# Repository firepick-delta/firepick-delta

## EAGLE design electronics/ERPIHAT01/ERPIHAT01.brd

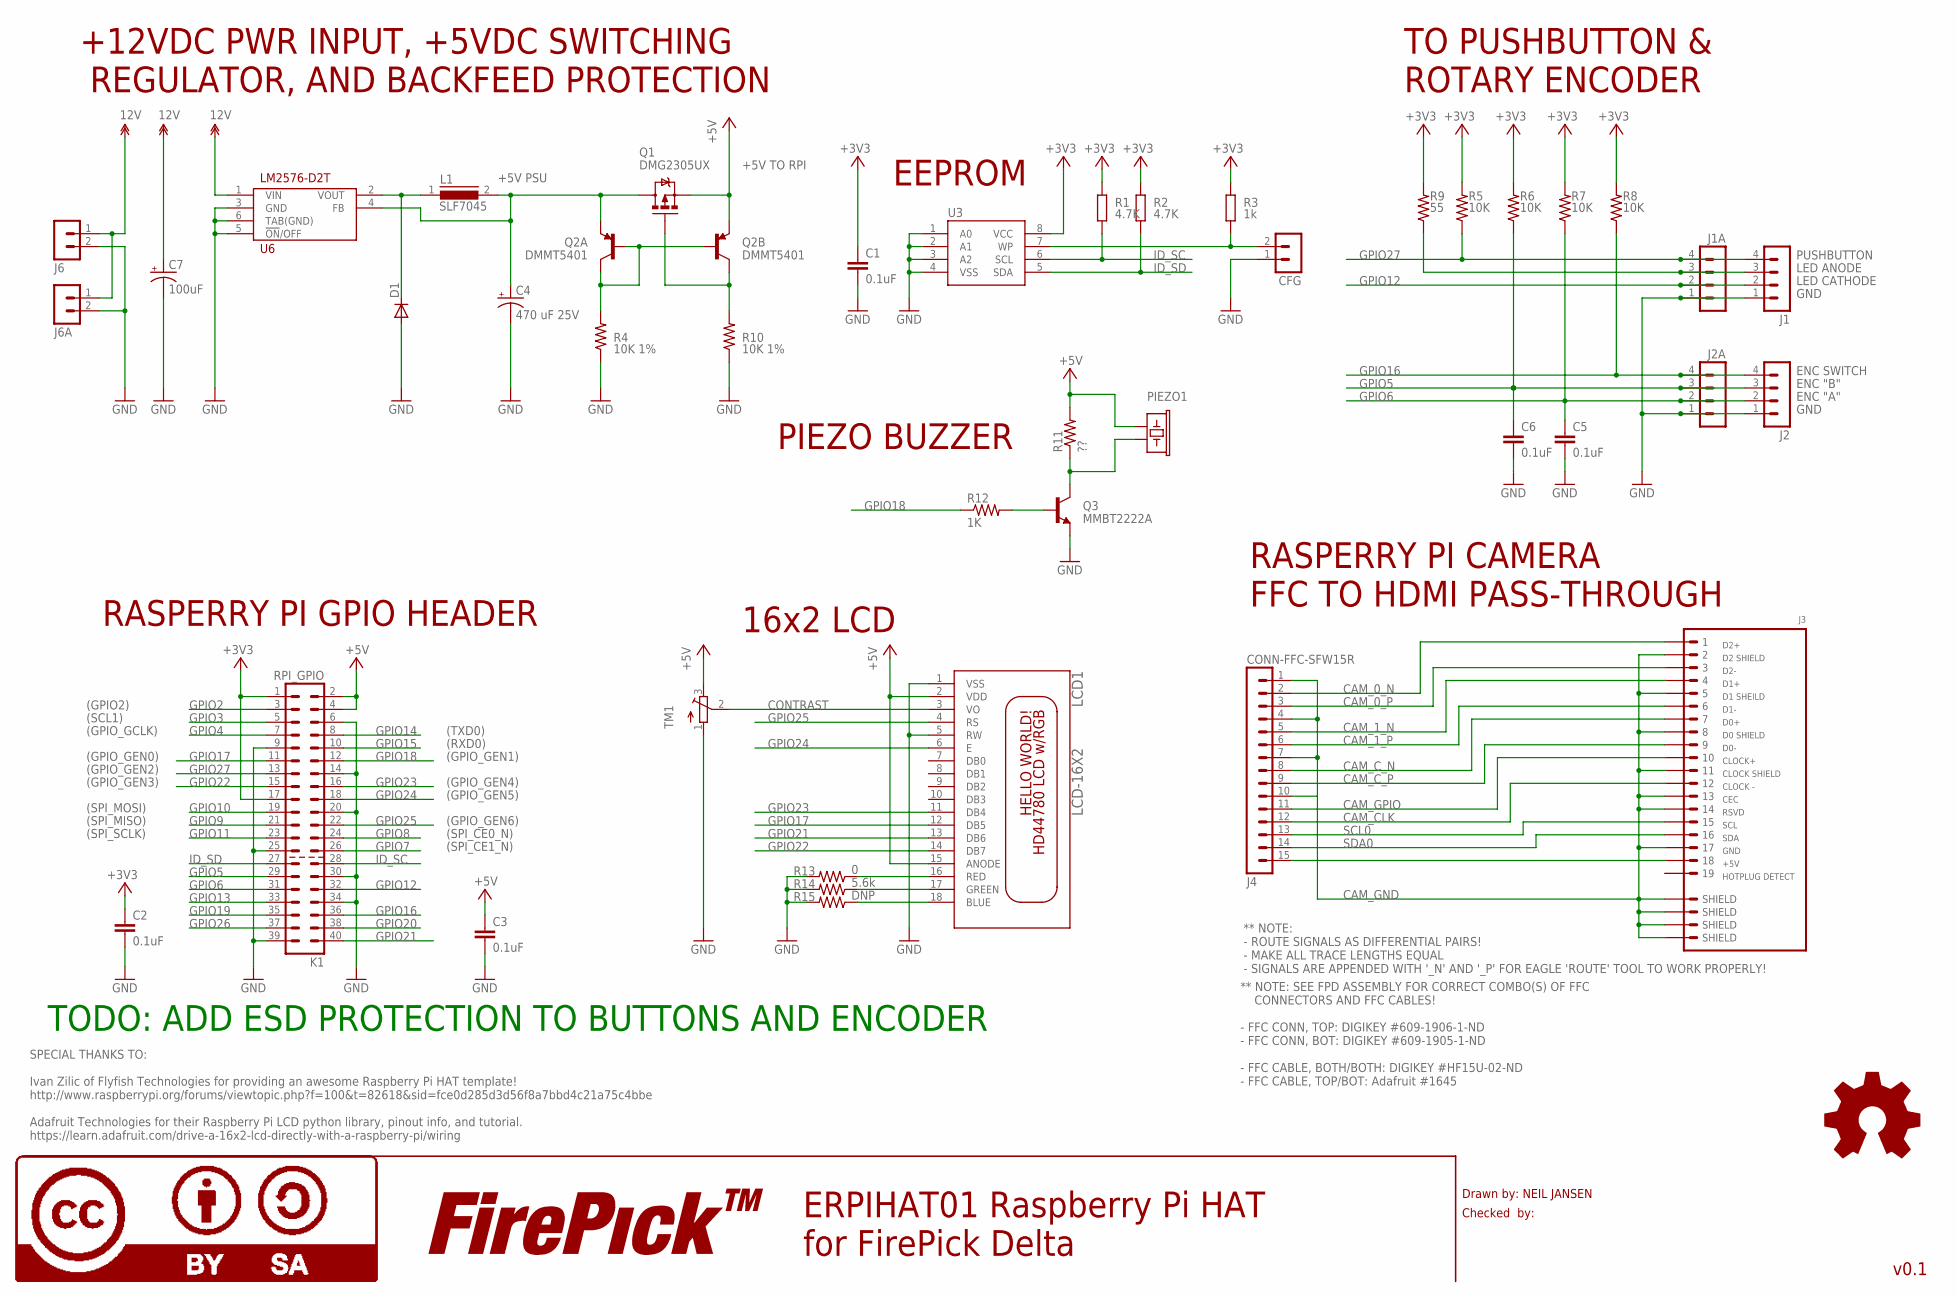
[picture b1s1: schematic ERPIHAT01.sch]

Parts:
C1, C2, C3: 0.1uF; C0805K
C4: 470 uF 25V; PANASONIC_D
C5, C6: 0.1uF; 0805
C7: 100uF; PANASONIC_D
CFG: MA02-1
D1: DIODE-DO-214AC; DO-214AC
J1, J2: CONN-RECT-4PINJST-PH-2MM; CONN-JST-PH_2.0MM_4PIN-SMT-RA
J1A, J2A: MA04-1
J3: CONN-HDMI; CON-HDMI-FCI-10029449-001RLF
J4: CONN-FFC-SFW15R; CON-FFC-SFW15R
J6: CONN-RECT-2PIN; CONN-JST_PH-2.0MM-2PIN-SMT-RA
J6A: MA02-1
K1: RPI_GPIO; PIN_20X2
L1: SLF7045
LCD1: LCD-16X2
LOGO1: LOGO-FIREPICK
LOGO2: LOGO-OSHWMEDIUM; LOGO-OSHW-MEDIUM
LOGO3: LOGO-CC-BY-SA
PIEZO1: BUZZERPTH; BUZZER-12MM
Q1: DMG2305UX; SOT23-3
Q2: DMMT5401; SOT23-6
Q3: MMBT2222A; SOT23-3
R1, R2: 4.7K; M0805; TOLERANCE 5%
R3: 1k; M0805; TOLERANCE 5%
R4, R10: 10K 1%; 0805
R5, R6, R7, R8: 10K; 0805
R9: 55; 0805
R11: ??; 0805
R12: 1K; 0805
R13: 0; 0805
R14: 5.6k; 0805
R15: DNP; 0805
TM1: TRIMPOTTC33X; TC33X
U3: EEPROM-I2CEIAJ; SO08-EIAJ
U6: LM2576-D2T; D2PAK

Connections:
12V: C7.+, J6.1, J6A.1, U6.1 (VIN)
+3V3: C1.1, C2.1, K1.1, K1.17, R1.2, R2.2, R3.2, R5.2, R6.2, R7.2, R8.2, R9.2, U3.8 (VCC)
+5V: C3.1, K1.2, K1.4, LCD1.2 (VDD), LCD1.15 (ANODE), PIEZO1.+ (1), Q1.2 (S), Q2.5 (E), R11.2, TM1.3 (E)
BLUE: LCD1.18 (BLUE), R15.1
BUZZ: PIEZO1.- (2), Q3.3 (C), R11.1
CAM_0_N: J3.1, J4.2
CAM_0_P: J3.3, J4.3
CAM_1_N: J3.4, J4.5
CAM_1_P: J3.6, J4.6
CAM_C_N: J3.7, J4.8
CAM_C_P: J3.9, J4.9
CAM_GND: J3.2, J3.5, J3.8, J3.11, J3.13, J3.14, J3.17, J3.SHIELD1 (SHIELD), J3.SHIELD2 (SHIELD), J3.SHIELD3 (SHIELD), J3.SHIELD4 (SHIELD), J4.1, J4.4, J4.7, J4.10
CAM_GPIOCLK_N: J3.10, J4.11
CAM_GPIOCLK_P: J3.12, J4.12
CAM_SCLSDA_N: J3.15, J4.13
CAM_SCLSDA_P: J3.16, J4.14
CONTRAST: LCD1.3 (VO), TM1.2 (S)
FEEDBACK: C4.+, L1.2, Q1.3 (D), Q2.6 (E), U6.4 (FB)
GND: C1.2, C2.2, C3.2, C4.-, C5.2, C6.2, C7.-, CFG.1, D1.A, J1.1, J1A.1, J2.1, J2A.1, J6.2, J6A.2, K1.6, K1.9, K1.14, K1.20, K1.25, K1.30, K1.34, K1.39, LCD1.1 (VSS), LCD1.5 (RW), Q3.2 (E), R4.1, R10.1, R13.2, R14.2, R15.2, TM1.1 (A), U3.1 (A0), U3.2 (A1), U3.3 (A2), U3.4 (VSS), U6.3 (GND), U6.5 (!ON!/OFF), U6.6 (TAB(GND))
GPIO2: K1.3
GPIO3: K1.5
GPIO4: K1.7
GPIO5: C6.1, J2.3, J2A.3, K1.29, R6.1
GPIO6: C5.1, J2.2, J2A.2, K1.31, R7.1
GPIO7: K1.26
GPIO8: K1.24
GPIO9: K1.21
GPIO10: K1.19
GPIO11: K1.23
GPIO12: J1.2, J1A.2, K1.32
GPIO13: K1.33
GPIO14: K1.8
GPIO15: K1.10
GPIO16: J2.4, J2A.4, K1.36, R8.1
GPIO17: K1.11, LCD1.12 (DB5)
GPIO18: K1.12, R12.1
GPIO19: K1.35
GPIO20: K1.38
GPIO21: K1.40, LCD1.13 (DB6)
GPIO22: K1.15, LCD1.14 (DB7)
GPIO23: K1.16, LCD1.11 (DB4)
GPIO24: K1.18, LCD1.6 (E)
GPIO25: K1.22, LCD1.4 (RS)
GPIO26: K1.37
GPIO27: J1.4, J1A.4, K1.13, R5.1
GREEN: LCD1.17 (GREEN), R14.1
ID_SC: K1.28, R1.1, U3.6 (SCL)
ID_SD: K1.27, R2.1, U3.5 (SDA)
unnamed: J3.18, J4.15
unnamed: Q2.1 (C), Q2.2 (B), Q2.3 (B), R4.2
unnamed: Q1.1 (G), Q2.4 (C), R10.2
unnamed: Q3.1 (B), R12.2
unnamed: CFG.2, R3.1, U3.7 (WP)
PANEL_LED_RED: J1.3, J1A.3, R9.1
RED: LCD1.16 (RED), R13.1
VOUT: D1.C, L1.1, U6.2 (VOUT)

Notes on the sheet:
Drawn by: NEIL JANSEN
Checked by:
SPECIAL THANKS TO: Ivan Zilic of Flyfish Technologies for providing an awesome Raspberry Pi HAT template! http://www.raspberrypi.org/forums/viewtopic.php?f=100&t=82618&sid=fce0d285d3d56f8a7bbd4c21a75c4bbe Adafruit Technologies for their Raspberry Pi LCD python library, pinout info, and tutorial. ht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
v0.1
(SPI_MOSI)
(SPI_MISO)
(SPI_SCLK)
(GPIO_GEN3)
(GPIO_GEN2)
(GPIO_GEN0)
(GPIO_GCLK)
(SCL1)
(GPIO2)
(TXD0)
(RXD0)
(GPIO_GEN1)
(GPIO_GEN4)
(GPIO_GEN5)
(GPIO_GEN6)
(SPI_CE0_N)
(SPI_CE1_N)
+5V TO RPI
+5V PSU
** NOTE: SEE FPD ASSEMBLY FOR CORRECT COMBO(S) OF FFC CONNECTORS AND FFC CABLES! - FFC CONN, TOP: DIGIKEY #609-1906-1-ND - FFC CONN, BOT: DIGIKEY #609-1905-1-ND - FFC CABLE, BOTH/BOTH: DIGIKEY #HF15U-02-ND - FFC CABLE, TOP/BOT: Adafruit #1645
PUSHBUTTON
GND
ENC "A"
ENC "B"
ENC SWITCH
LED ANODE
LED CATHODE
** NOTE: - ROUTE SIGNALS AS DIFFERENTIAL PAIRS! - MAKE ALL TRACE LENGTHS EQUAL - SIGNALS ARE APPENDED WITH '_N' AND '_P' FOR EAGLE 'ROUTE' TOOL TO WORK PROPERLY!
CAM_GPIO
CAM_CLK
SCL0
SDA0
RASPERRY PI CAMERA FFC TO HDMI PASS-THROUGH
16x2 LCD
TO PUSHBUTTON & ROTARY ENCODER
EEPROM

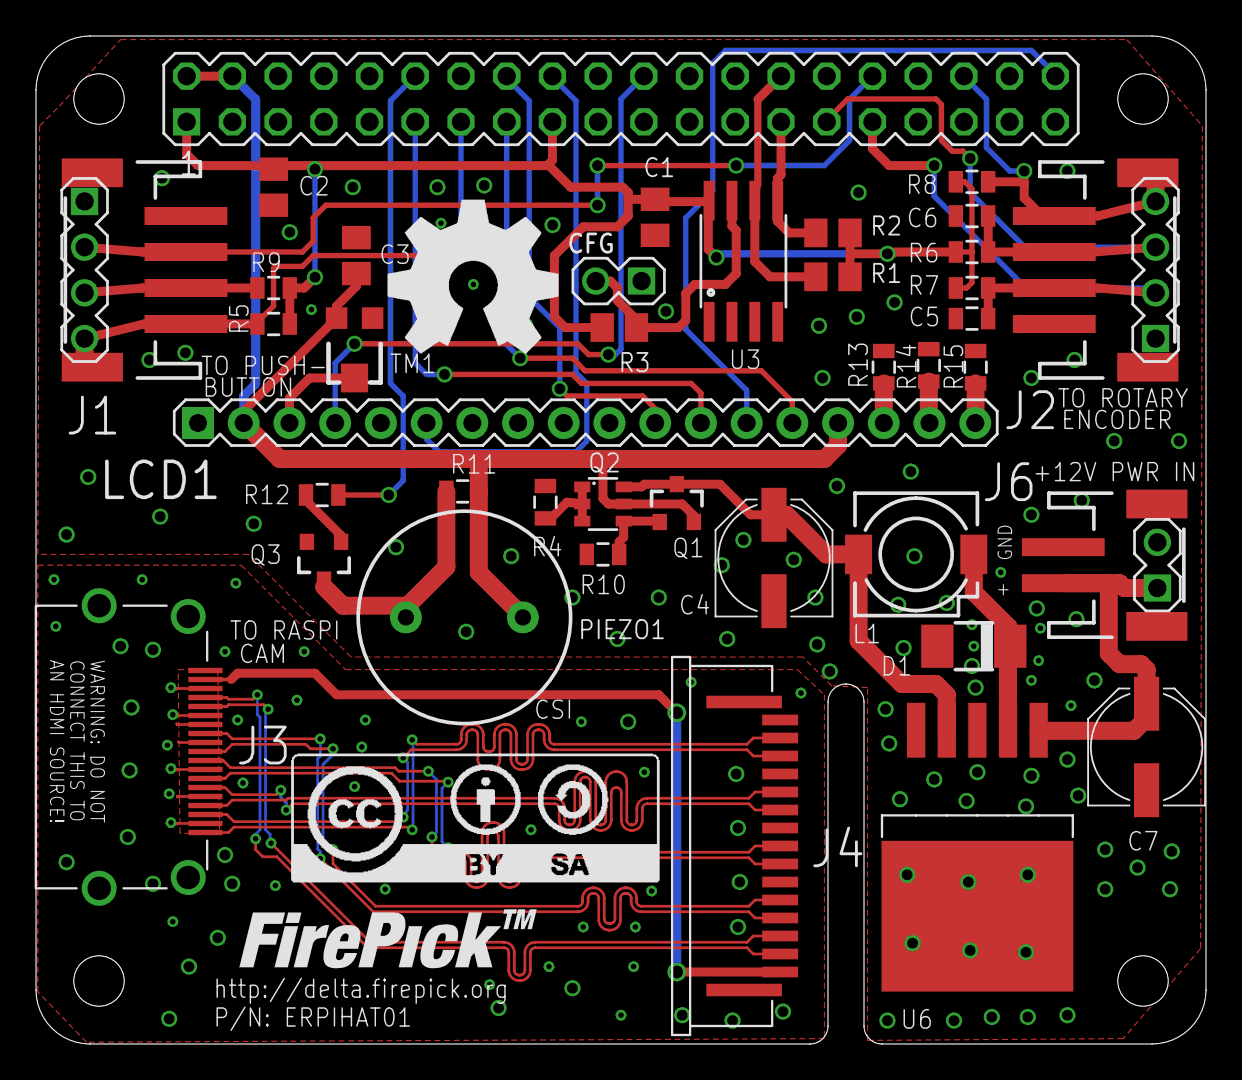
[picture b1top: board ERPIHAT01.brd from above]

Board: 2 copper layers, 65.0 x 56.0 mm, 45 parts (0 on the bottom side), 42 nets.

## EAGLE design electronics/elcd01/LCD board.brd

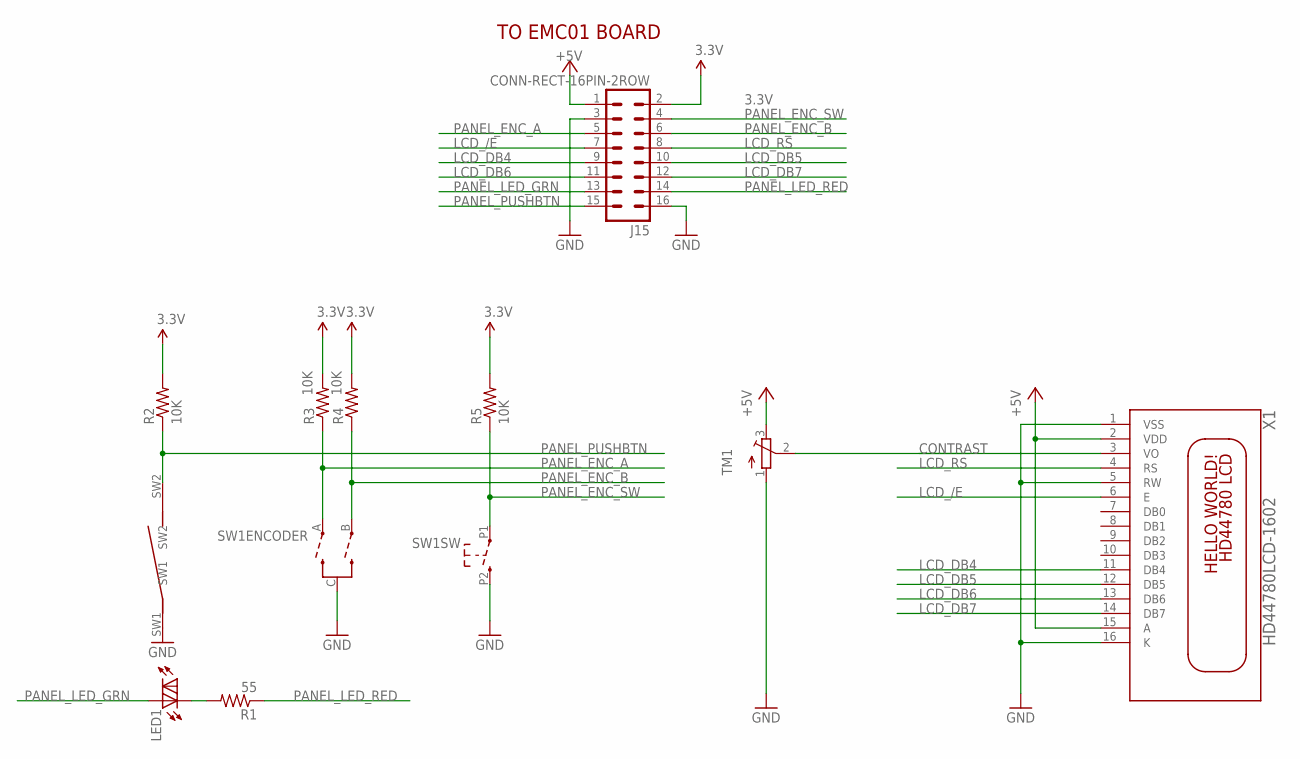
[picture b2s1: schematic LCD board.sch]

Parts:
J15: CONN-RECT-16PIN-2ROW; CONN-RECT-2.54MM-16PIN-2ROW-SMTH
LED1: LED-BUTTON; ELAST_PAD_SQUARE_10MM_5.4MM_4X4GRID
R1: 55; 0805
R2, R3, R4, R5: 10K; 0805
SW1: ENCODER_SW1-PEC12; PEC12_INCREMENTAL_ENCODER
TM1: TRIMPOTTC33X; TC33X
X1: HD44780LCD-1602; LCD1602

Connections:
3.3V: J15.2, R2.2, R3.2, R4.2, R5.2
+5V: J15.1, TM1.3 (E), X1.2 (VDD), X1.15 (A)
GND: J15.3, J15.16, LED1.SW1, SW1.C, SW1.P2 (2), TM1.1 (A), X1.1 (VSS), X1.5 (RW), X1.16 (K)
LCD_/E: J15.7, X1.6 (E)
LCD_DB4: J15.9, X1.11 (DB4)
LCD_DB5: J15.10, X1.12 (DB5)
LCD_DB6: J15.11, X1.13 (DB6)
LCD_DB7: J15.12, X1.14 (DB7)
LCD_RS: J15.8, X1.4 (RS)
unnamed: TM1.2 (S), X1.3 (VO)
unnamed: LED1.K (C), R1.2
PANEL_ENC_A: J15.5, R3.1, SW1.A
PANEL_ENC_B: J15.6, R4.1, SW1.B
PANEL_ENC_SW: J15.4, R5.1, SW1.P1 (1)
PANEL_LED_GRN: J15.13, LED1.A1 (A)
PANEL_LED_RED: J15.14, R1.1
PANEL_PUSHBTN: J15.15, LED1.SW2, R2.1

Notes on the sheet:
TO EMC01 BOARD

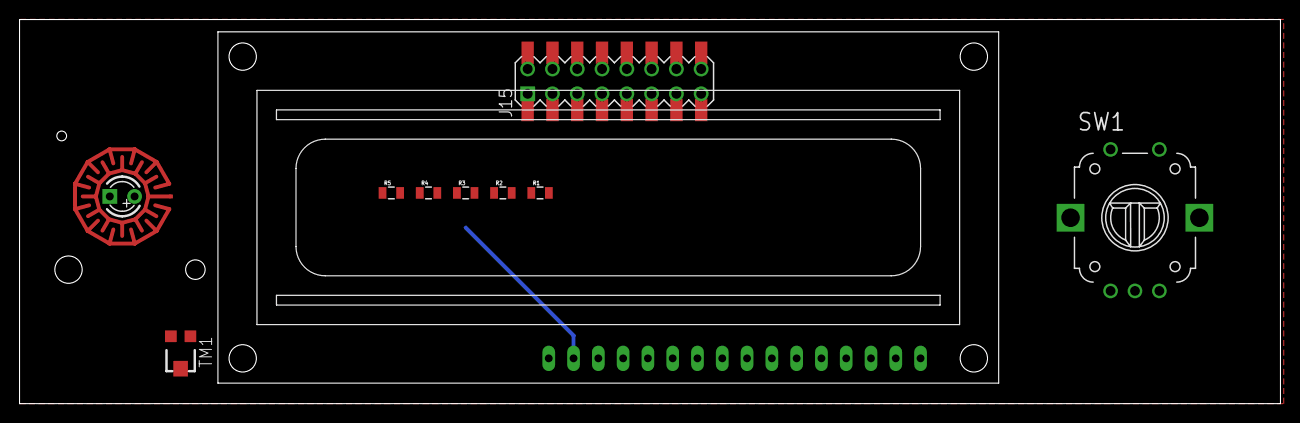
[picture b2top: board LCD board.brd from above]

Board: 2 copper layers, 129.2 x 39.4 mm, 10 parts (0 on the bottom side), 17 nets.

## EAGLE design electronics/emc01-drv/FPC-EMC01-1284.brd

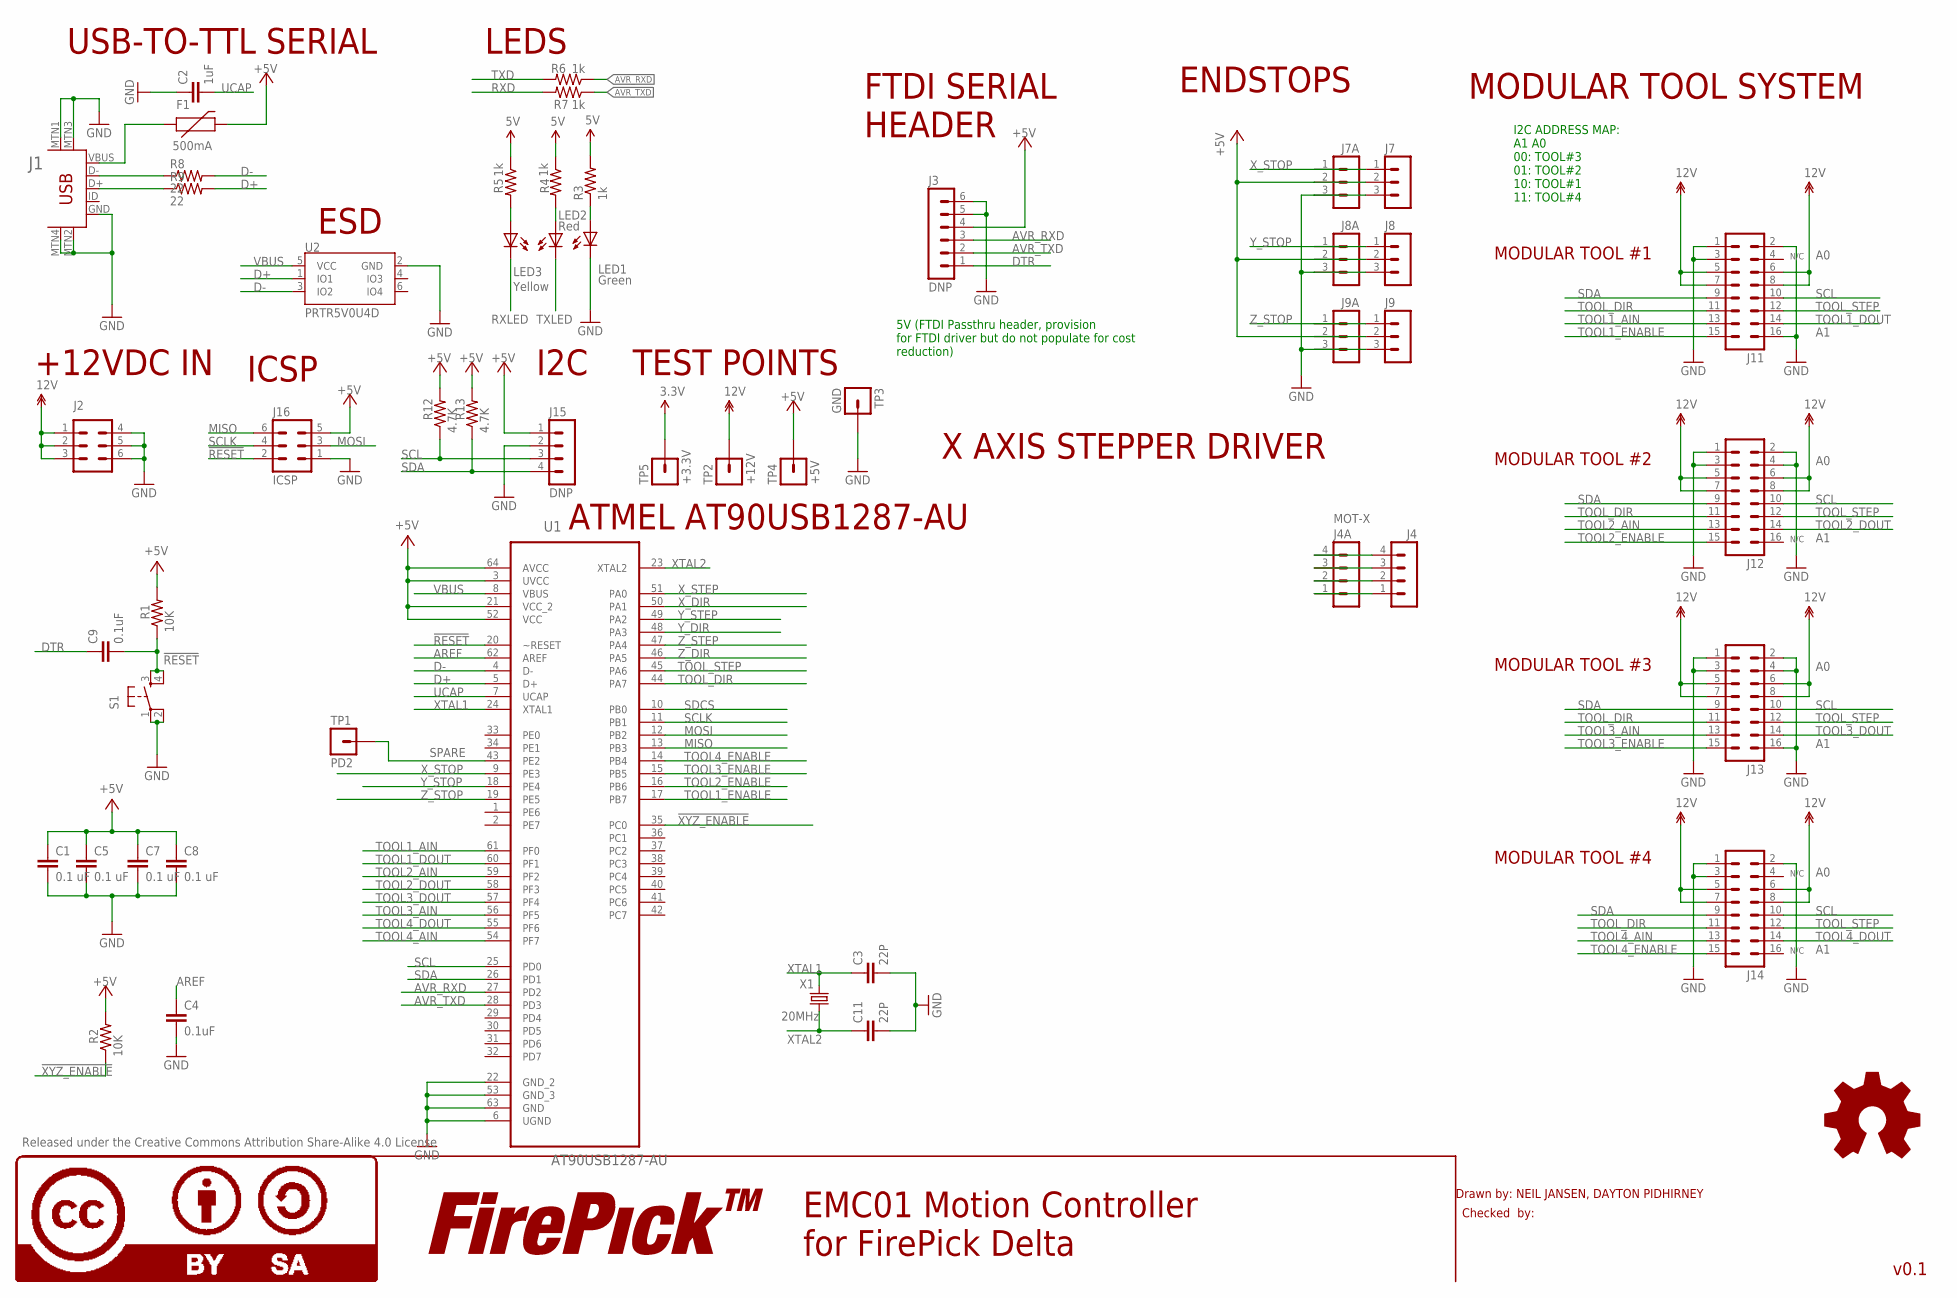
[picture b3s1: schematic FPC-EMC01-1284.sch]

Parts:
C1, C5, C7, C8: 0.1 uF; 0805
C2: 1uF; 0805
C3, C11: 22P; 0805
C4, C9: 0.1uF; 0805
F1: 500mA; PTC-1206
J1: USB-MINIB-5PIN; USB-MINIB
J2: CONN-MOLEX-MICROFIT-6PIN; CONN-MOLEX-MINIFIT-6PIN-2ROW
J3: DNP; MA06-1
J4: MA04-1
J4A: MOT-X; CONN-JST-PH_2.0MM_4PIN-SMT-RA
J7, J8, J9: MA03-1
J7A, J8A, J9A: CONN-RECT-3PINJST_PH_2MM; CONN-JST_PH-2.0MM-3PIN-SMT-RA
J11, J12, J13, J14: CONN-RECT-16PIN-2ROW; CONN-RECT-2.54MM-16PIN-2ROW-SMTH
J15: DNP; MA04-1
J16: ICSP; CONN-RECT-2.54MM-6-PIN-2ROW-SMTH
LED1: Green; LED-1206-NO_SILK
LED2: Red; LED-1206-NO_SILK
LED3: Yellow; LED-1206-NO_SILK
LOGO4: LOGO-FIREPICKLARGE; LOGO-FIREPICK
LOGO5: LOGO-OSHWMEDIUM; LOGO-OSHW-MEDIUM
LOGO6: LOGO-CC-BY-SALARGE; LOGO-CC-BY-SA
R1, R2: 10K; 0805
R3, R4, R5, R6, R7: 1k; 0805
R8, R9: 22; 0805
R12, R13: 4.7K; 0805
S1: TAC_SWITCHSMD; TACTILE_SWITCH_SMD
TP1: PD2; CON-TESTPOINT
TP2: +12V; CON-TESTPOINT
TP3: GND; CON-TESTPOINT
TP4: +5V; CON-TESTPOINT
TP5: +3.3V; CON-TESTPOINT
U1: AT90USB1287-AU; QFP80P1600X1600X120-64N
U2: PRTR5V0U4D; SOT23-6
X1: 20MHz; CTS406

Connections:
3.3V: TP5.1
12V: J2.1, J2.2, J2.3, J11.5, J11.6, J11.7, J11.8, J12.5, J12.6, J12.7, J12.8, J13.5, J13.6, J13.7, J13.8, J14.5, J14.6, J14.7, J14.8, TP2.1
!RESET: C9.2, J16.2, R1.1, S1.3, S1.4, U1.20 (~RESET)
!XYZ_ENABLE: R2.1, U1.35 (PC0)
+5V: C1.1, C5.1, C7.1, C8.1, F1.2, J3.4, J7.2, J7A.2, J8.2, J8A.2, J9.2, J9A.2, J15.1, J16.5, R1.2, R2.2, R3.2, R4.1, R5.1, R12.2, R13.2, TP4.1, U1.3 (UVCC), U1.21 (VCC_2), U1.52 (VCC), U1.64 (AVCC)
AREF: C4.1, U1.62 (AREF)
AVR_RXD: J3.3, R6.1, U1.27 (PD2)
AVR_TXD: J3.2, R7.1, U1.28 (PD3)
D+: R9.2, U1.5 (D+), U2.1 (IO1)
D-: R8.2, U1.4 (D-), U2.3 (IO2)
DTR: C9.1, J3.1
GND: C1.2, C2.1, C3.2, C4.2, C5.2, C7.2, C8.2, C11.2, J1.GND, J1.MTN1 (MTN2), J1.MTN2 (MTN3), J1.MTN3 (MTN1), J1.MTN4, J2.4, J2.5, J2.6, J3.5, J3.6, J7.3, J7A.3, J8.3, J8A.3, J9.3, J9A.3, J11.1, J11.2, J11.3, J11.16, J12.1, J12.2, J12.3, J12.4, J13.1, J13.2, J13.3, J13.4, J13.16, J14.1, J14.2, J14.3, J15.2, J16.1, LED1.C, S1.1, S1.2, TP3.1, U1.6 (UGND), U1.22 (GND_2), U1.53 (GND_3), U1.63 (GND), U2.2 (GND)
MISO: J16.6, U1.13 (PB3)
MOSI: J16.3, U1.12 (PB2)
unnamed: J1.D-, R8.1
unnamed: J1.D+, R9.1
unnamed: LED1.A, R3.1
unnamed: LED2.A, R4.2
unnamed: LED3.A, R5.2
RXD: R7.2
RXLED: LED3.C
SCL: J11.10, J12.10, J13.10, J14.10, J15.3, R12.1, U1.25 (PD0)
SCLK: J16.4, U1.11 (PB1)
SDA: J11.9, J12.9, J13.9, J14.9, J15.4, R13.1, U1.26 (PD1)
SDCS: U1.10 (PB0)
SPARE: TP1.1, U1.43 (PE2)
TOOL1_AIN: J11.13, U1.61 (PF0)
TOOL1_DOUT: J11.14, U1.60 (PF1)
TOOL1_ENABLE: J11.15, U1.17 (PB7)
TOOL2_AIN: J12.13, U1.59 (PF2)
TOOL2_DOUT: J12.14, U1.58 (PF3)
TOOL2_ENABLE: J12.15, U1.16 (PB6)
TOOL3_AIN: J13.13, U1.56 (PF5)
TOOL3_DOUT: J13.14, U1.57 (PF4)
TOOL3_ENABLE: J13.15, U1.15 (PB5)
TOOL4_AIN: J14.13, U1.54 (PF7)
TOOL4_DOUT: J14.14, U1.55 (PF6)
TOOL4_ENABLE: J14.15, U1.14 (PB4)
TOOL_DIR: J11.11, J12.11, J13.11, J14.11, U1.44 (PA7)
TOOL_STEP: J11.12, J12.12, J13.12, J14.12, U1.45 (PA6)
TXD: R6.2
TXLED: LED2.C
UCAP: C2.2, U1.7 (UCAP)
VBUS: U1.8 (VBUS), U2.5 (VCC)
VUSB: F1.1, J1.VBUS
X1A: J4.2, J4A.2
X1B: J4.1, J4A.1
X2A: J4.3, J4A.3
X2B: J4.4, J4A.4
XTAL1: C3.1, U1.24 (XTAL1), X1.3 (2)
XTAL2: C11.1, U1.23 (XTAL2), X1.1
X_DIR: U1.50 (PA1)
X_STEP: U1.51 (PA0)
X_STOP: J7.1, J7A.1, U1.9 (PE3)
Y_DIR: U1.48 (PA3)
Y_STEP: U1.49 (PA2)
Y_STOP: J8.1, J8A.1, U1.18 (PE4)
Z_DIR: U1.46 (PA5)
Z_STEP: U1.47 (PA4)
Z_STOP: J9.1, J9A.1, U1.19 (PE5)

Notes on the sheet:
I2C ADDRESS MAP: A1 A0 00: TOOL#3 01: TOOL#2 10: TOOL#1 11: TOOL#4
MODULAR TOOL #4
MODULAR TOOL #3
MODULAR TOOL #2
MODULAR TOOL #1
5V (FTDI Passthru header, provision for FTDI driver but do not populate for cost reduction)
Drawn by: NEIL JANSEN, DAYTON PIDHIRNEY
Checked by:
v0.1
EMC01 Motion Controller for FirePick Delta
ATMEL AT90USB1287-AU
USB-TO-TTL SERIAL
X AXIS STEPPER DRIVER
ENDSTOPS
MODULAR TOOL SYSTEM
FTDI SERIAL HEADER
+12VDC IN
ICSP
I2C
TEST POINTS
N/C
Released under the Creative Commons Attribution Share-Alike 4.0 License
ESD
LEDS

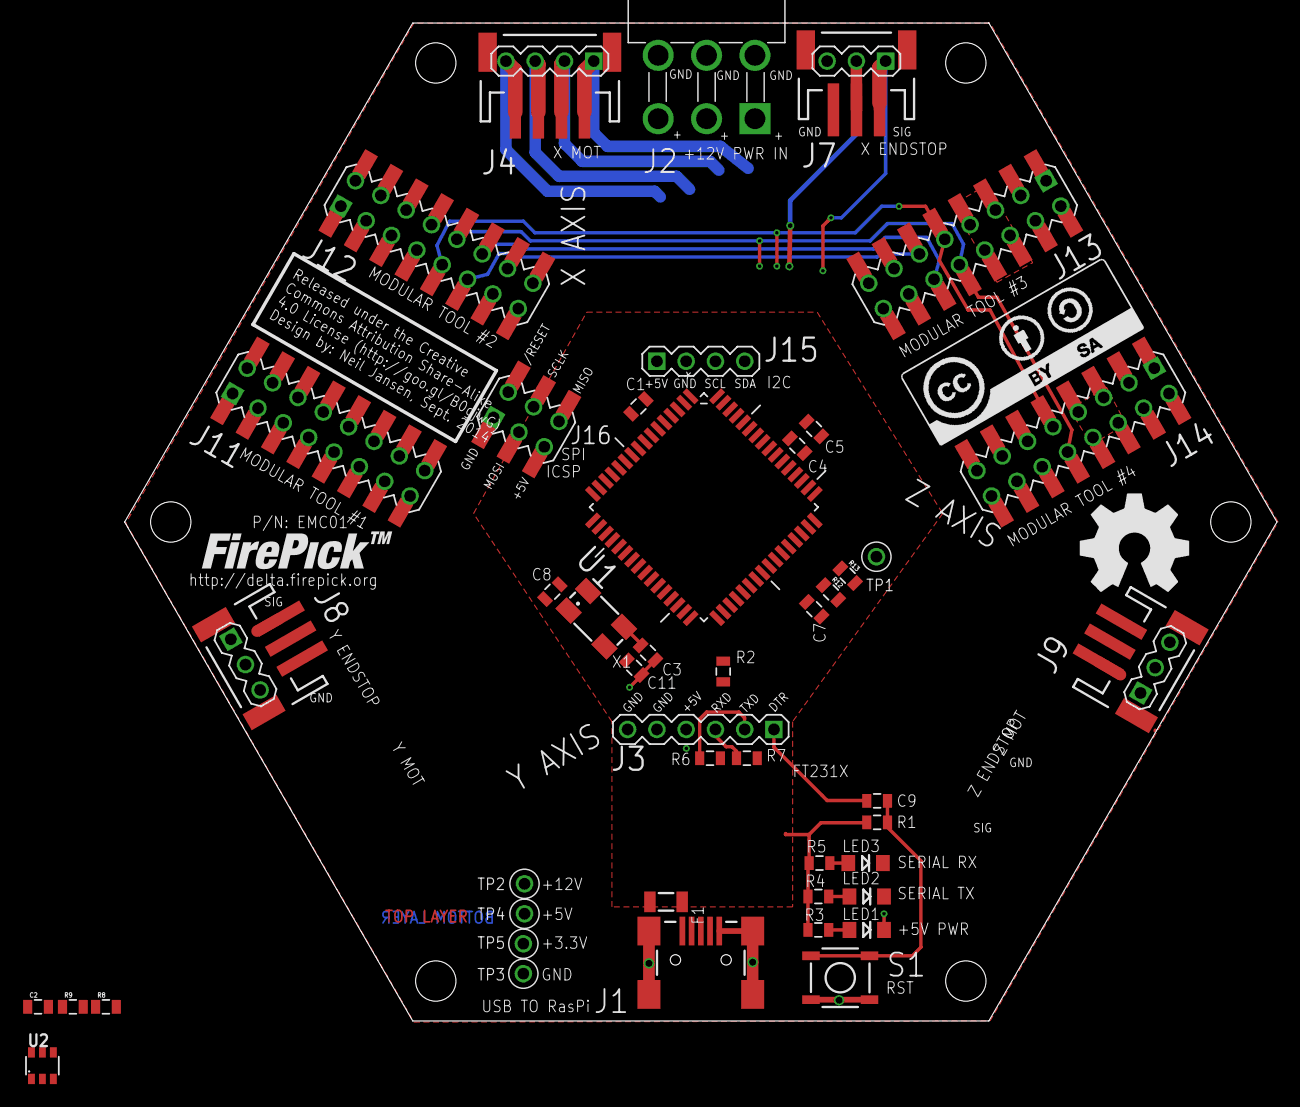
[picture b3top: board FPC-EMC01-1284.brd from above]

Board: 2 copper layers, 100.0 x 86.6 mm, 53 parts (0 on the bottom side), 48 nets.

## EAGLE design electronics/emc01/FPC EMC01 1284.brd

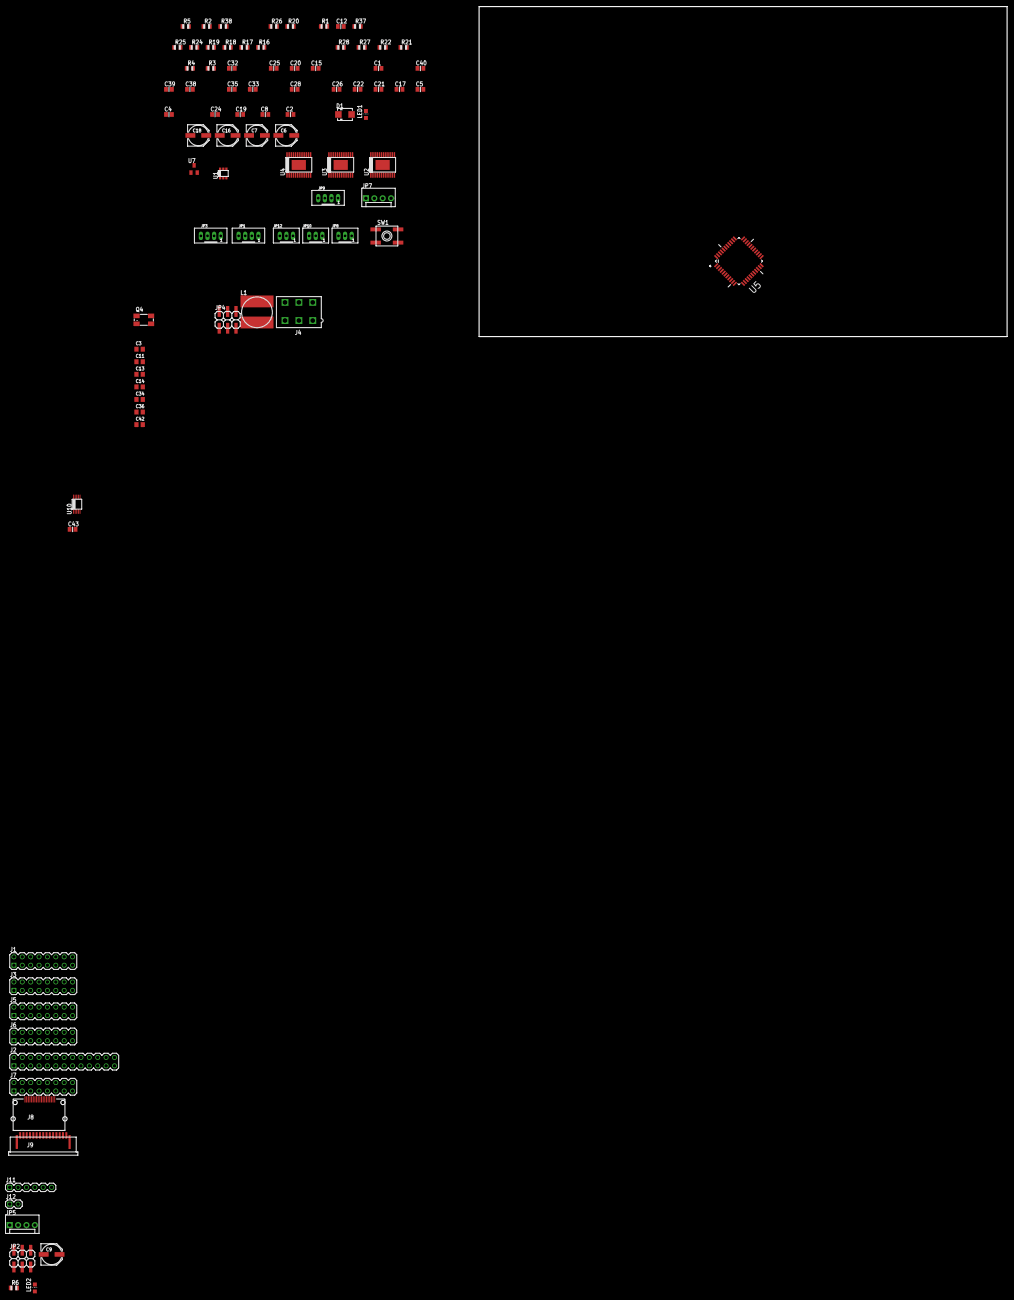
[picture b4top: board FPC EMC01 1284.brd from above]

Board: 2 copper layers, 160.0 x 100.0 mm, 89 parts (0 on the bottom side), 95 nets, no tracks yet.

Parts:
C1: 22uF; CAPC2012X145AN
C2, C8, C19, C24: 0.22uF; CAPC2012X145AN
C3, C11: 22pf; C805
C4, C5, C17, C21, C22, C26, C28, C33, C35, C38, C39, C40, C43: 0.1uF; CAPC2012X145AN
C6, C7, C9, C16, C18: 100uF; PANASONIC_D
C12: 1uF; CAPC2012X145AN
C13, C14, C34, C36, C42: C805
C15, C20, C25, C32: 10uF; CAPC2012X145AN
D1: SMA
J1, J3, J5, J6, J7: MA08-2
J2: MA13-2
J4: PCIE; 5566-6
J8: CON-HDMI; CON-HDMI-FCI-10029449-001RLF
J9: CON-FFC-SFW15R
J11: MA06-1
J12: MA02-1
JP1: MOT-Y; JST_B4B-PH_HEADER
JP2, JP4: ICSP; 2X03SMD
JP3: MOT-Z; JST_B4B-PH_HEADER
JP5, JP7: I2C; MOLEX-1X4
JP8: Y-STOP; JST_B3B-PH_HEADER
JP9: MOT-X; JST_B4B-PH_HEADER
JP10: Z-STOP; JST_B3B-PH_HEADER
JP12: X-STOP; JST_B3B-PH_HEADER
L1: 47uH; SDR1006
LED1, LED2: PWR; CHIP-LED0805
Q4: CTS406
R1, R6: 330; R0805
R2, R20, R26: 10k; R0805
R3, R4, R21, R22, R27, R28: 100k; R0805
R5: 100K; R0805
R16, R17, R18, R19, R24, R25: 0.11; R0805
R37: 5.6k; R0805
R38: 1k; R0805
SW1: SPST_TACT-EVQQ2; EVQ-Q2
U1: LM2841; TSOT6
U2, U3, U4: A4982; TSSOP-24
U5: ATMEGA1284P-AU; QFP80P1200X1200X120-44N
U7: AP7313; SOT23C
U10: MCP4728; MSOP10

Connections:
12V: C4.1, C6.+, C7.+, C9.+, C12.1, C16.+, C18.+, C21.1, C26.1, C28.1, C33.1, C35.1, J1.1, J1.2, J3.1, J3.2, J4.1, J4.2, J4.3, J5.1, J5.2, J6.1, J6.2, U1.4, U1.5, U2.16, U2.21, U3.16, U3.21, U4.16, U4.21
!RESET: JP2.2, JP4.2
!XYZ-ENABLE: R3.2, R21.2, R27.2, U2.23, U3.23, U4.23
+3V3: C32.1, U7.2
+3V3_RASPI: J2.1, J2.17, J7.2
+5V: C1.1, C13.2, C14.2, C15.2, C20.2, C25.2, C34.2, C36.2, C43.2, J1.14, J2.2, J2.4, J3.7, J3.14, J5.8, J5.14, J6.7, J6.8, J6.14, J7.1, J11.4, JP2.5, JP4.5, JP5.4, JP7.4, JP8.P2, JP10.P2, JP12.P2, L1.P$2, R1.2, R3.1, R4.1, R5.2, R6.2, R21.1, R22.1, R27.1, R28.1, R37.1, U2.5, U2.6, U2.10, U3.5, U3.6, U3.10, U4.5, U4.6, U4.10, U5.5, U5.17, U5.27, U5.38, U7.1, U10.1, U10.4
AREF: C42.2, U5.29
AVR_RXD: J11.3, U5.9
AVR_TXD: J11.2, U5.10
GND: C1.2, C3.2, C6.-, C7.-, C8.1, C9.-, C11.2, C12.2, C13.1, C14.1, C15.1, C16.-, C18.-, C19.1, C20.1, C24.1, C25.1, C28.2, C32.2, C33.2, C34.1, C35.2, C36.1, C38.2, C39.2, C40.2, C42.1, C43.1, D1.A, J1.3, J1.4, J1.7, J1.8, J1.15, J1.16, J2.6, J2.9, J2.14, J2.20, J2.25, J3.3, J3.4, J3.8, J3.15, J3.16, J4.4, J4.5, J4.6, J5.3, J5.4, J5.7, J5.15, J5.16, J6.3, J6.4, J6.15, J6.16, J7.3, J7.16, J11.5, J11.6, JP2.1, JP4.1, JP5.3, JP7.3, JP8.P3, JP10.P3, JP12.P3, LED1.C, LED2.C, R2.2, R16.2, R17.2, R18.2, R19.2, R20.2, R24.2, R25.2, R26.2, R38.2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
LCD_/E: J2.18, J7.7
LCD_DB4: J2.16, J7.9
LCD_DB5: J2.11, J7.10
LCD_DB6: J2.13, J7.11
LCD_DB7: J2.15, J7.12
LCD_RS: J2.22, J7.8
MISO: JP2.6, JP4.6, U5.2
MOSI: JP2.3, JP4.3, U5.1
unnamed: JP9.P4, U2.18
unnamed: C5.2, U2.1
unnamed: C5.1, U2.2
unnamed: R2.1, U2.8
unnamed: R17.1, U2.17
unnamed: R18.1, U2.20
unnamed: C4.2, U2.3
unnamed: JP9.P3, U2.19
unnamed: C8.2, U2.4
unnamed: JP9.P2, U2.15
unnamed: R4.2, U2.7, U2.9
unnamed: R37.2, R38.1, U1.3
unnamed: JP9.P1, U2.22
unnamed: JP1.P3, U3.19
unnamed: JP1.P4, U3.18
unnamed: JP1.P2, U3.15
unnamed: C17.2, U3.1
unnamed: C17.1, U3.2
unnamed: JP1.P1, U3.22
unnamed: R19.1, U3.20
unnamed: R20.1, U3.8
unnamed: C19.2, U3.4
unnamed: R22.2, U3.7, U3.9
unnamed: C21.2, U3.3
unnamed: R16.1, U3.17
unnamed: JP3.P4, U4.18
unnamed: JP3.P3, U4.19
unnamed: JP3.P2, U4.15
unnamed: C22.2, U4.1
unnamed: C22.1, U4.2
unnamed: R24.1, U4.17
unnamed: R25.1, U4.20
unnamed: R26.1, U4.8
unnamed: C24.2, U4.4
unnamed: R28.2, U4.7, U4.9
unnamed: C26.2, U4.3
unnamed: JP3.P1, U4.22
unnamed: C2.1, D1.C, L1.P$1, U1.6
unnamed: C2.2, U1.1
PANEL_ENC_A: J2.26, J7.5
PANEL_ENC_B: J2.21, J7.6
PANEL_ENC_SW: J2.24, J7.4
PANEL_LED_GRN: J2.19, J7.13
PANEL_LED_RED: J2.12, J7.14
PANEL_PUSHBTN: J2.23, J7.15
RASPI_RXD: J2.10, J12.1
RASPI_TXD: J2.8, J12.2
RESET: R5.1, SW1.B, SW1.B', U5.4
SCL: J1.6, J3.6, J5.6, J6.6, JP5.1, JP7.1, U10.2
SCLK: JP2.4, JP4.4, U5.3
SDA: J1.5, J3.5, J5.5, J6.5, JP5.2, JP7.2, U10.3
TOOL1_AIN: J1.13, U5.37
TOOL1_DOUT: J1.12, U5.33
TOOL1_ENABLE: J1.9, U5.14
TOOL2_AIN: J3.13, U5.36
TOOL2_DOUT: J3.12, U5.32
TOOL2_ENABLE: J3.9, U5.13
TOOL3_AIN: J5.13, U5.35
TOOL3_DOUT: J5.12, U5.31
TOOL3_ENABLE: J5.9, U5.12
TOOL4_AIN: J6.13, U5.34
TOOL4_DOUT: J6.12, U5.30
TOOL4_ENABLE: J6.9, U5.11
TOOL_DIR: J1.11, J3.11, J5.11, J6.11, U5.40
TOOL_STEP: J1.10, J3.10, J5.10, J6.10, U5.41
VREF_X: C39.1, U2.12, U10.9
VREF_Y: C38.1, U3.12, U10.8
VREF_Z: C40.1, U4.12, U10.7
X-DIR: U2.14, U5.24
X-STEP: U2.11, U5.16
X-STOP: JP12.P1, U5.21
XTAL1: C3.1, Q4.3, U5.8
XTAL2: C11.1, Q4.1
Y-DIR: U3.14, U5.26
Y-STEP: U3.11, U5.25
Y-STOP: JP8.P1, U5.22
Z-STOP: JP10.P1, U5.23

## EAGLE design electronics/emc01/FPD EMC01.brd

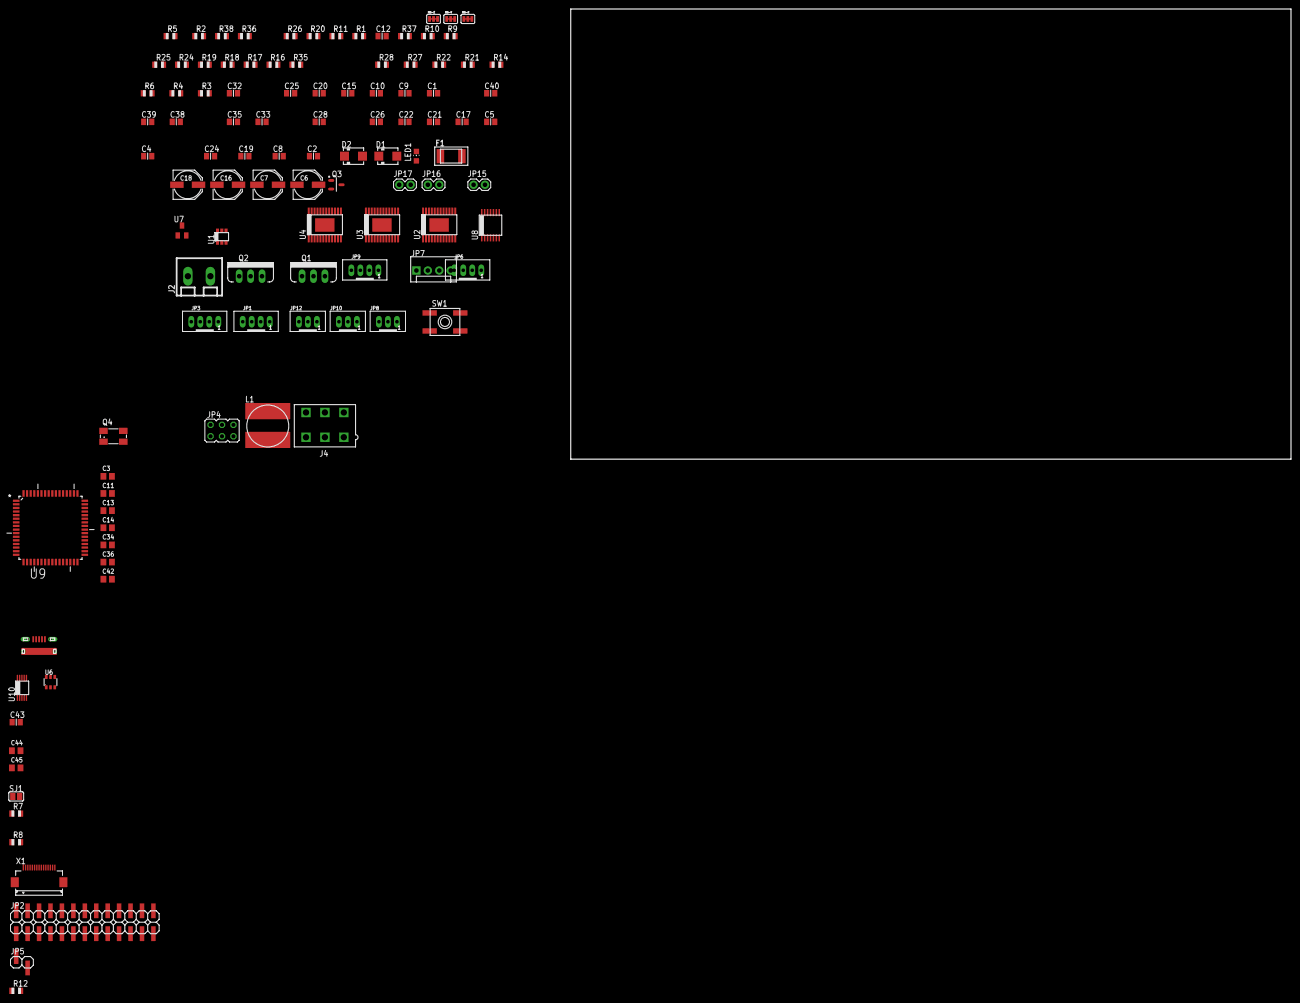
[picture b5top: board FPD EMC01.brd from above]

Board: 2 copper layers, 281.9 x 143.2 mm, 108 parts (0 on the bottom side), 89 nets, no tracks yet.

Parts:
C1: 22uF; CAPC2012X145AN
C2, C8, C19, C24: 0.22uF; CAPC2012X145AN
C3, C11, C13, C14, C34, C36, C42: C805
C4, C5, C17, C21, C22, C26, C28, C33, C35, C38, C39, C40, C43: 0.1uF; CAPC2012X145AN
C6, C7, C16, C18: 100uF; PANASONIC_D
C9, C10, C15, C20, C25, C32: 10uF; CAPC2012X145AN
C12: 1uF; CAPC2012X145AN
C44: 1UF; C805
C45: 100NF; C805
D1, D2: SMA
F1: MINISMDC
J2: PHOENIX-5MM-2POS
J3: USB-MICRO-PTH; USB-MICROB-PTH
J4: PCIE; 5566-6
JP1: MOT-Y; JST_B4B-PH_HEADER
JP2: RPI_GPIO; 2X13SMD
JP3: MOT-Z; JST_B4B-PH_HEADER
JP4: ICSP; JP3Q
JP5: BOOT; 1X02SMD
JP6: HOTEND; JST_B4B-PH_HEADER
JP7: I2C; MOLEX-1X4
JP8: Y-STOP; JST_B3B-PH_HEADER
JP9: MOT-X; JST_B4B-PH_HEADER
JP10: Z-STOP; JST_B3B-PH_HEADER
JP12: X-STOP; JST_B3B-PH_HEADER
JP15: B-THERM; 1X02
JP16: E-THERM; 1X02
JP17: FAN; 1X02
L1: 47uH; SDR1006
LED1: PWR; CHIP-LED0805
MS-X: SJ_3_CONNECTED
MS-Y: SJ_3_CONNECTED
MS-Z: SJ_3_CONNECTED
Q1, Q2: RFP30N06LE; TO220V
Q3: RFP30N06LE; SOT95P280X135-3N
Q4: CTS406
R1: 330; R0805
R2, R20, R26: 10k; R0805
R3, R4, R6, R14, R21, R22, R27, R28, R35: 100k; R0805
R5, R12: 100K; R0805
R7, R8: 22; R0805
R9, R10: 4.7k; R0805
R11, R36: 100; R0805
R16, R17, R18, R19, R24, R25: 0.11; R0805
R37: 5.6k; R0805
R38: 1k; R0805
SJ1: SJ
SW1: SPST_TACT-EVQQ2; EVQ-Q2
U1: LM2841; TSOT6
U2, U3, U4: A4982; TSSOP-24
U6: PRTR5V0U4D; SOT23-6
U7: AP7313; SOT23C
U8: TXB0104; TSSOP14
U9: AT90USB1287-AU; QFP80P1600X1600X120-64N
U10: MCP4728; MSOP10
X1: 15-Pin FFC For Cam; FH12-15S-0.5SH

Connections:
12V: C4.1, C6.+, C7.+, C12.1, C16.+, C18.+, C21.1, C26.1, C28.1, C33.1, C35.1, J2.P$1, J4.1, J4.2, J4.3, JP6.P3, JP6.P4, JP17.1, U1.4, U1.5, U2.16, U2.21, U3.16, U3.21, U4.16, U4.21
!HOTBED: R11.1, R35.1
!HOTEND: R6.1, R36.1
!PWM-FAN: Q3.1, R14.1
!X-ENABLE: R3.2, U2.23
!Y-ENABLE: R21.2, U3.23
!Z-ENABLE: R27.2, U4.23
+3V3: C32.1, U7.2, U8.1, U8.8
+5V: C1.1, C13.2, C14.2, C15.2, C20.2, C25.2, C34.2, C36.2, C43.2, JP4.5, JP7.4, JP8.P2, JP10.P2, JP12.P2, L1.P$2, MS-X.2, MS-Y.2, MS-Z.2, R1.2, R3.1, R4.1, R5.2, R9.2, R10.2, R12.2, R21.1, R22.1, R27.1, R28.1, R37.1, SJ1.2, U2.10, U3.10, U4.10, U7.1, U8.14, U9.21, U9.52, U9.64, U10.1, U10.4
ALF: JP5.2, R12.1, U9.43
AREF: C42.2, U9.62
B-THERM: C9.2, JP15.1, R10.1, U9.61
D+: R8.1, U9.5
D-: R7.1, U9.4
E-THERM: C10.2, JP16.1, R9.1
GND: C1.2, C3.2, C6.-, C7.-, C8.1, C9.1, C10.1, C11.2, C12.2, C13.1, C14.1, C15.1, C16.-, C18.-, C19.1, C20.1, C24.1, C25.1, C28.2, C32.2, C33.2, C34.1, C35.2, C36.1, C38.2, C39.2, C40.2, C42.1, C43.1, C44.2, C45.1, D1.A, D2.A, J3.GND, J3.GND1, J3.GND2, J3.GND3, J3.GND4, J3.GND5, J4.4, J4.5, J4.6, JP4.1, JP5.1, JP7.3, JP8.P3, JP10.P3, JP12.P3, JP15.2, JP16.2, LED1.C, Q1.3, Q2.3, Q3.2, R2.2, R6.2, R14.2, R16.2, R17.2, R18.2, R19.2, R20.2, R24.2, R25.2, R26.2, R35.2, R38.2, SW1.A, SW1.A', U1.2, U2.13, U2.24, U2.PAD, U3.13, U3.24, U3.PAD, U4.13, U4.24, U4.PAD, U6.2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
HOTBED-GND: J2.P$2, Q2.2
HOTEND-GND: JP6.P1, JP6.P2, Q1.2
MCU_DN: J3.D-, R7.2, U6.3
MCU_DP: J3.D+, R8.2, U6.1
MISO: JP4.6, U8.13, U9.13
MOSI: JP4.3, U8.11, U9.12
unnamed: LED1.A, R1.1
unnamed: D2.C, F1.P$2, Q3.3
unnamed: F1.P$1, JP17.2
unnamed: Q2.1, R11.2
unnamed: JP9.P3, U2.18
unnamed: C5.2, U2.1
unnamed: C5.1, U2.2
unnamed: R2.1, U2.8
unnamed: R17.1, U2.17
unnamed: R18.1, U2.20
unnamed: C4.2, U2.3
unnamed: JP9.P4, U2.15
unnamed: C8.2, U2.4
unnamed: JP9.P2, U2.19
unnamed: R4.2, U2.7, U2.9
unnamed: R37.2, R38.1, U1.3
unnamed: JP9.P1, U2.22
unnamed: JP1.P2, U3.19
unnamed: JP1.P1, U3.22
unnamed: MS-X.1, U2.5
unnamed: MS-X.3, U2.6
unnamed: C17.2, U3.1
unnamed: C17.1, U3.2
unnamed: R19.1, U3.20
unnamed: R20.1, U3.8
unnamed: C19.2, U3.4
unnamed: R22.2, U3.7, U3.9
unnamed: C21.2, U3.3
unnamed: R16.1, U3.17
unnamed: JP3.P2, U4.19
unnamed: MS-Y.1, U3.5
unnamed: MS-Y.3, U3.6
unnamed: C22.2, U4.1
unnamed: C22.1, U4.2
unnamed: R24.1, U4.17
unnamed: R25.1, U4.20
unnamed: R26.1, U4.8
unnamed: C24.2, U4.4
unnamed: R28.2, U4.7, U4.9
unnamed: C26.2, U4.3
unnamed: JP3.P1, U4.22
unnamed: MS-Z.1, U4.5
unnamed: MS-Z.3, U4.6
unnamed: Q1.1, R36.2
unnamed: C2.1, D1.C, L1.P$1, U1.6
unnamed: C2.2, U1.1
RESET: R5.1, SW1.B, SW1.B', U9.20
SCL: JP7.1, U9.25, U10.2
SCLK: JP4.4, U8.12
SDA: JP7.2, U9.26, U10.3
SDCS: U8.10, U9.10
VBUS: C45.2, J3.VBUS, SJ1.1, U6.5, U9.8
VCAP: C44.1, U9.7
VREF_X: C39.1, U2.12, U10.9
VREF_Y: C38.1, U3.12, U10.8
VREF_Z: C40.1, U4.12, U10.7
X-DIR: U2.14, U9.50
X-STEP: U2.11, U9.51
X-STOP: JP12.P1, U9.9
XTAL1: C3.1, Q4.3, U9.24
XTAL2: C11.1, Q4.1, U9.23
Y-DIR: U3.14, U9.48
Y-STEP: U3.11, U9.49
Y-STOP: JP8.P1, U9.14
Z-DIR: U4.14, U9.46
Z-STEP: U4.11, U9.47
Z-STOP: JP10.P1, U9.18

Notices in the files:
electronics/emc02/EMC02.brd:
CC-BY-SA 4.0 license
electronics/emodhs01/HotStick.brd:
Laine Walker-Avina (C) 2013
parts and their libraries:
SparkFun-Passives: Licensing: Creative Commons ShareAlike 4.0 International - https://creativecommons.org/licenses/by-sa/4.0
SparkFun-Capacitors: Licensing: CC v3.0 Share-Alike You are welcome to use this library for commercial purposes.
SparkFun: http://creativecommons.org/licenses/by-sa/3.0
